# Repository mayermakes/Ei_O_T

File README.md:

# Ei_O_T
Breadboard Friendly ESP32-S2 Development Kit / Breakout

All EI.O.T Boards are manufactured in either Europe or USA. There are NO genuine Boards made in Asia, and there probably never will be.
This is necessary to ensure quality and safety for the applications developed with our Development Kits and breakout boards.
USB-OTG functionality is built in Hardware wise. 
The Board can be assembled in two ways allowing dominantly left and right handed Developers to optimally use it, also by flipping it upside down you can choose to have the USB cable stick out the top or bottom.

Safety and Handling Notice: 
This product is exclusivelly intended as an utility device for development under laboratory conditions. For use or operation specialist knowledge is required.
Assembly by yourself as askilled technician is required. The provided Firmware is only example code to confirm a correctly executed flashing process.

The project is Licensed CC-BY-SA, the Provided Gerbers are marked with registered Trademarks owned by the original developer or IP owners.
Violation of these rights is not covered by the Open source license or any other license.
If you want to manufacture the Boards for your own private use, you can freely do so. If you intent to bring this design into circulation of any kind you can apply for a distribution license and will be provided an individual version.

The Circuitpython firmware is provided under CC_BY_SA license adhering to the original file it was based on.
You need to follow this guide to be able to flash it:
https://circuitpython.readthedocs.io/en/6.1.x/ports/esp32s2/README.html

For usage with the Arduino IDE please follow the latest tutorial to install the ESP32S2 based boards on Arduino IDE.
To programm the board please choose "ESP32S2DevModule" from the boards list.
Put the board into download mode by holding down the Flash button while pressing reset.
EI.O.T does not automatically reset by design, you need to push the reset button yourself, this is to avoid serial transmittion errors while developing IOT applications.

This evaluation board/kit is intended for use for engineering development, evaluation or demonstration use only. It is not considered by MAYER MAKES e.U. to be a product for End-user /consumer use.  Therefore it may not meet those requirements and is only suitable for use by technically skilled professionals.****

The Files and Documentation are provided as is without any warranty.
MAYER MAKES is an internationally registered Trademark of MAYER MAKES e.U., unauthorized use is prohibited

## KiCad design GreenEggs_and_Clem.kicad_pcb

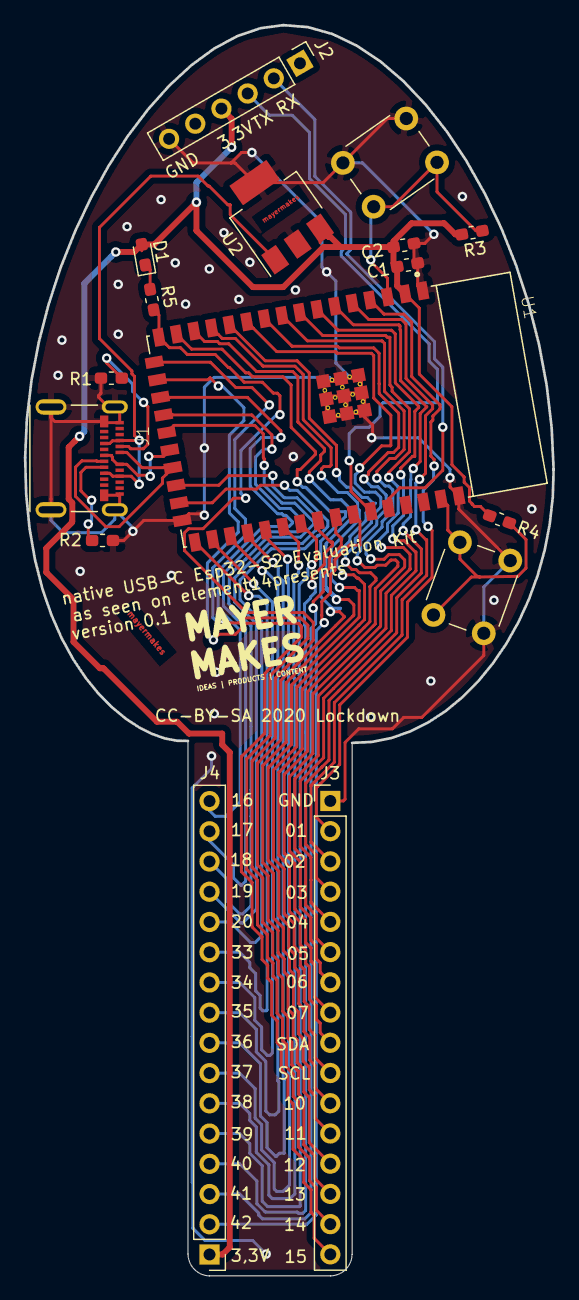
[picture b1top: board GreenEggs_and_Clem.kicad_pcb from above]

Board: 2 copper layers, 44.4 x 105.0 mm, 16 parts (0 on the bottom side), 42 nets.

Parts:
C1: 0,1uF; C_0603_1608Metric_Pad1.05x0.95mm_HandSolder
C2: 10uF; C_0603_1608Metric_Pad1.05x0.95mm_HandSolder
D1: LED 0603; LED_0603_1608Metric_Pad1.05x0.95mm_HandSolder
FLASH: flash; SW_PUSH_6mm
J1: 105450-0101; MOLEX_105450-0101
J2: Conn_01x06_Female; PinHeader_1x06_P2.54mm_Vertical
J3, J4: Conn_01x16; PinHeader_1x16_P2.54mm_Vertical
R1, R2: 5k1; R_0603_1608Metric_Pad1.05x0.95mm_HandSolder
R3, R4: 10k; R_0603_1608Metric_Pad1.05x0.95mm_HandSolder
R5: 220; R_0603_1608Metric_Pad1.05x0.95mm_HandSolder
RESET: reset; SW_PUSH_6mm
U1: ESP32-S2-WROOM; XCVR_ESP32-S2-WROOM
U2: MCP1825S; SOT-223-3_TabPin2

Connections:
/01: J3.2, U1.4
/02: J3.3, U1.5
/03: J3.4, U1.6
/04: J3.5, U1.7
/05: J3.6, U1.8
/06: J3.7, U1.9
/07: J3.8, U1.10
/10: J3.11, U1.13
/11: J3.12, U1.14
/12: J3.13, U1.15
/13: J3.14, R5.2, U1.16
/14: J3.15, U1.17
/15: J3.16, U1.18
/16: J4.16, U1.19
/17: J4.15, U1.20
/18: J4.14, U1.21
/21: J4.13, U1.24
/26: J4.12, U1.25
/33: J4.11, U1.27
/34: J4.10, U1.28
/35: J4.9, U1.29
/36: J4.8, U1.30
/37: J4.7, U1.31
/38: J4.6, U1.32
/39: J4.5, U1.33
/40: J4.4, U1.34
/41: J4.3, U1.35
/42: J4.2, U1.36
D+: J1.A6, J1.B6, U1.23
D-: J1.A7, J1.B7, U1.22
GND: C1.1, C2.1, FLASH.1, J1.A1, J1.A12, J1.B1, J1.B12, J1.S1, J1.S2, J1.S3, J1.S4, J2.6, J3.1, R1.2, R2.2, RESET.1, U1.1, U1.26, U1.42, U1.43.1, U1.43.2, U1.43.3, U1.43.4, U1.43.5, U1.43.6, U1.43.7, U1.43.8, U1.43.9, U1.43.10, U1.43.11, U1.43.12, U1.43.13, U1.43.14, U1.43.15, U1.43.16, U1.43.17, U1.43.18, U1.43.19, U1.43.20, U1.43.21, U2.2
unnamed: D1.1, R5.1
unnamed: J1.A5, R1.1
unnamed: J1.B5, R2.1
RX: J2.2, U1.38
SCL: J3.10, U1.12
SDA: J3.9, U1.11
TX: J2.3, U1.37
VCC_ESP: C1.2, C2.2, D1.2, J2.4, J4.1, R3.2, R4.2, U1.2, U2.3
Vbus: J1.A4, J1.A9, J1.B4, J1.B9, U2.1
~FLASH: FLASH.2, R3.1, U1.3
~RESET: R4.1, RESET.2, U1.41

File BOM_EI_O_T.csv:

Source:,/media/mayermakes/b79b1a1f-57e0-435e-a345-7f3b9296dbeb/kicad/EI_O_T/GreenEggs_and_Clem/GreenEggs_and_Clem.sch,,,,,,,,,
Date:,Fr 26 Feb 2021 21:29:43,,,,,,,,,
Tool:,Eeschema 5.1.5+dfsg1-2build2,,,,,,,,,
Generator:,/usr/share/kicad/plugins/bom_csv_grouped_by_value.py,,,,,,,,,
Component Count:,16,,,,,,,,,
,,,,,,,,,,
Individual Components:,,,,,,,,,,
,,,,,,,,,,
,,,,,,,,,,
,,,,,,,,,,
Collated Components:,,,,,,,,,,
,,,,,,,,,,
Item,Qty,Reference(s),Value,LibPart,Footprint,Manufacturer Partnumber,Manufacturer,Supplier,Order Number,Remarks
1,1,C1,"0,1uF",Device:C,Capacitor_SMD:C_0603_1608Metric_Pad1.05x0.95mm_HandSolder,~,Generic,,,
2,1,C2,10uF,Device:C,Capacitor_SMD:C_0603_1608Metric_Pad1.05x0.95mm_HandSolder,~,Generic,,,
3,1,D1,LED 0603,Device:LED,LED_SMD:LED_0603_1608Metric_Pad1.05x0.95mm_HandSolder,~,Generic,,,
4,1,J1,105450-0101,105450-0101:105450-0101,Molex_USB-C:MOLEX_105450-0101,105450-0101,Molex,Farnell,2524076,USB Shielded I/O Receptacle; Type C; Right Angle; Surface Mount; Gold over Nickel
5,1,J2,Conn_01x06_Female,Connector:Conn_01x06_Female,Connector_PinHeader_2.54mm:PinHeader_1x06_P2.54mm_Vertical,~,Generic,,,
6,2,"J3, J4",Conn_01x16,Connector_Generic:Conn_01x16,Connector_PinHeader_2.54mm:PinHeader_1x16_P2.54mm_Vertical,~,Generic,,,
7,2,"R1, R2",5k1,Device:R,Resistor_SMD:R_0603_1608Metric_Pad1.05x0.95mm_HandSolder,~,Generic,,,
8,2,"R3, R4",10k,Device:R,Resistor_SMD:R_0603_1608Metric_Pad1.05x0.95mm_HandSolder,~,Generic,,,
9,1,R5,220,Device:R,Resistor_SMD:R_0603_1608Metric_Pad1.05x0.95mm_HandSolder,~,Generic,,,
10,1,SW1,reset,Switch:SW_Push,Button_Switch_THT:SW_PUSH_6mm,~,Generic,,,
11,1,SW2,flash,Switch:SW_Push,Button_Switch_THT:SW_PUSH_6mm,~,Generic,,,
12,1,U1,ESP32-S2-WROOM,ESP32-S2-WROOM:ESP32-S2-WROOM,ESP32S2:XCVR_ESP32-S2-WROOM,ESP32-S2-WROOM(M22S2H3200PH3Q0) ,Espressif ,Mouser,356-ESP32S2WRM3200PH ,
13,1,U2,MCP1825S-3302E/DB,Regulator_Linear:MCP1825S,Package_TO_SOT_SMD:SOT-223-3_TabPin2,MCP1825S-3302E/DB ,Mikrochip,Farnell,1578404,

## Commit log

2022-01-05 Kicad files added
    Be aware that MAYER MAKES is a internationally registered Trademark, unauthorized use is prohibited.

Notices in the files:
GreenEggs_and_Clem.kicad_pcb:
CC-BY-SA 2020 Lockdown
